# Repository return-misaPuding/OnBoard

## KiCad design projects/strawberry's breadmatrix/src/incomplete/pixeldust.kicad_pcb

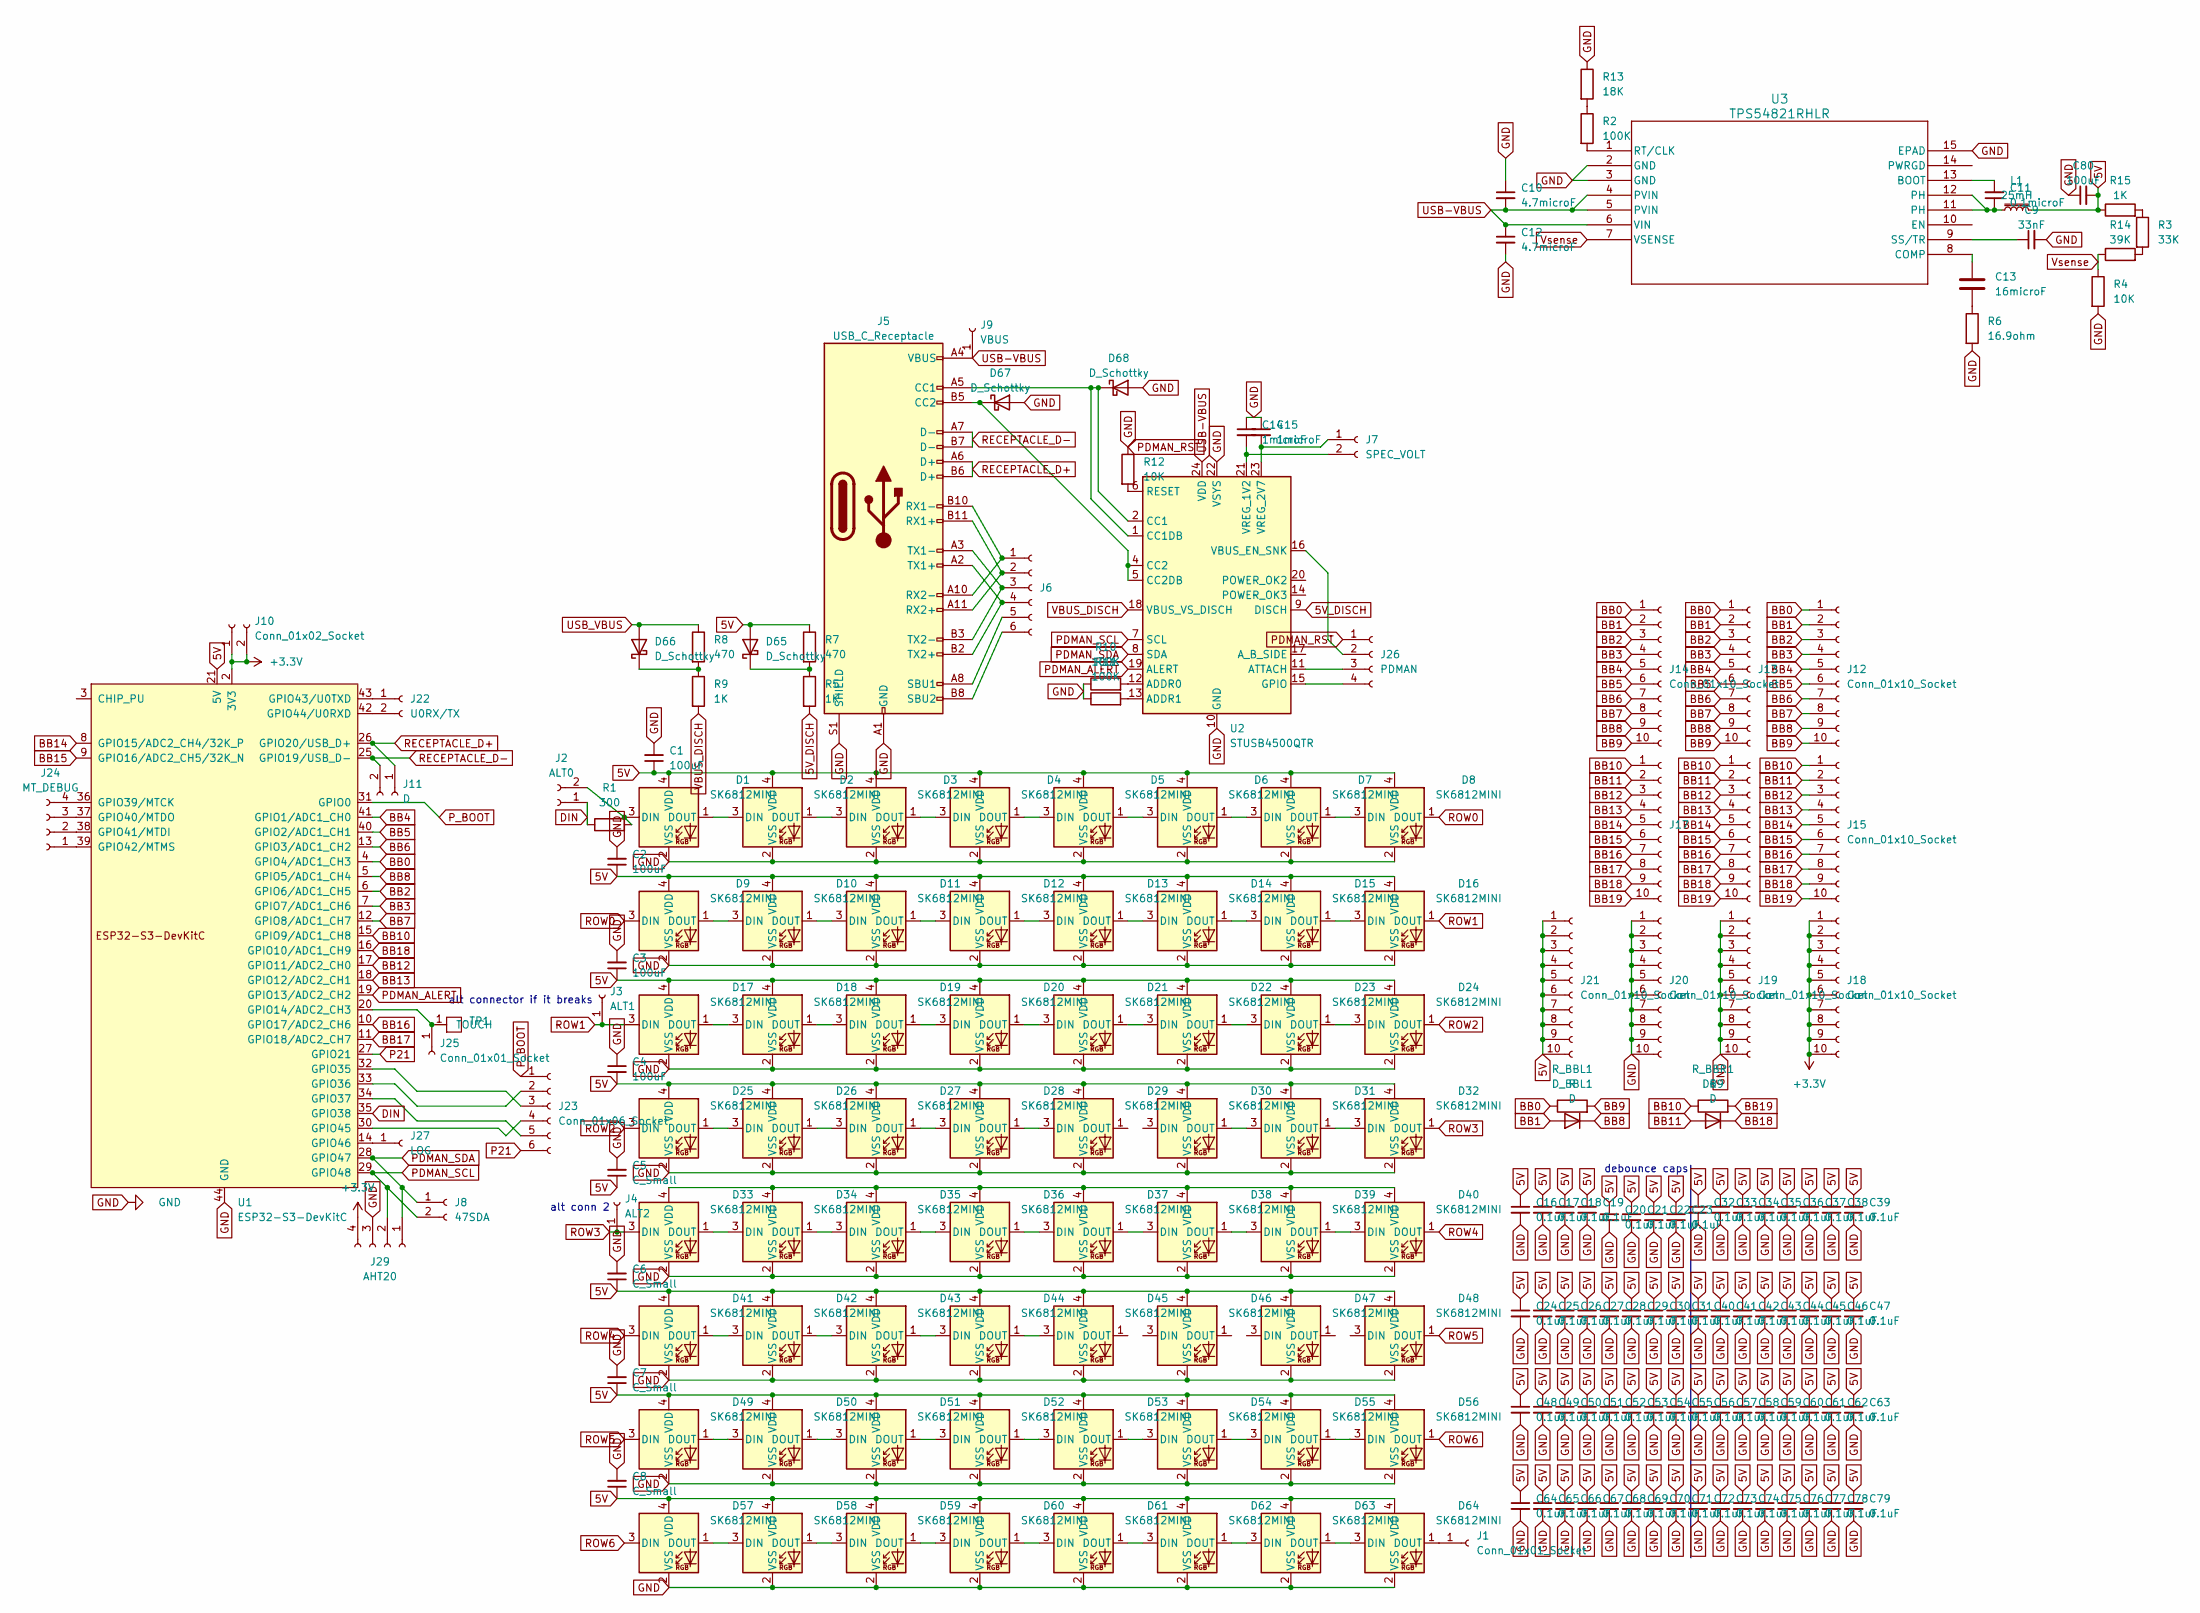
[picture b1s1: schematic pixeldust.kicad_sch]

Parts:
C1, C2, C3, C4, C80: 100uF; C_1206_3216Metric
C5, C6, C7, C8: C_Small; C_1206_3216Metric
C9: 33nF; C_0402_1005Metric
C10, C12: 4.7microF; C_1206_3216Metric_Pad1.33x1.80mm_HandSolder
C11: 0.1microF; C_0402_1005Metric
C13: 16microF; CP_Axial_L10.0mm_D4.5mm_P15.00mm_Horizontal
C14, C15: 1microF; C_0402_1005Metric
C16, C17, C18, C19, C20, C21, C22, C23, C24, C25, C26, C27, C28, C29, C30, C31, C32, C33, C34, C35, C36, C37, C38, C39, C40, C41, C42, C43, C44, C45, C46, C47, C48, C49, C50, C51, C52, C53, C54, C55, C56, C57, C58, C59, C60, C61, C62, C63, C64, C65, C66, C67, C68, C69, C70, C71, C72, C73, C74, C75, C76, C77, C78, C79: 0.1uF; C_0402_1005Metric
D1, D2, D3, D4, D5, D6, D7, D8, D9, D10, D11, D12, D13, D14, D15, D16, D17, D18, D19, D20, D21, D22, D23, D24, D25, D26, D27, D28, D29, D30, D31, D32, D33, D34, D35, D36, D37, D38, D39, D40, D41, D42, D43, D44, D45, D46, D47, D48, D49, D50, D51, D52, D53, D54, D55, D56, D57, D58, D59, D60, D61, D62, D63, D64: SK6812MINI; LED_SK6812MINI_PLCC4_3.5x3.5mm_P1.75mm
D65, D66: D_Schottky; D_DO-41_SOD81_P7.62mm_Horizontal
D67, D68: D_Schottky; D_DO-41_SOD81_P3.81mm_Vertical_AnodeUp
D69: D; D_SOD-123
D_BBL1: D; D_DO-41_SOD81_P3.81mm_Vertical_AnodeUp
J1, J25: Conn_01x01_Socket; PinSocket_1x01_P2.54mm_Vertical
J2: ALT0; PinSocket_1x02_P1.00mm_Vertical
J3: ALT1; PinSocket_1x01_P2.54mm_Vertical
J4: ALT2; PinSocket_1x01_P2.54mm_Vertical
J5: USB_C_Receptacle; USB_C_Receptacle_Amphenol_12401610E4-2A
J6: USBC_RX/TX; PinSocket_2x03_P1.27mm_Vertical
J7: SPEC_VOLT; PinSocket_1x02_P1.00mm_Vertical
J8: 47SDA; PinSocket_1x02_P1.00mm_Vertical
J9: VBUS; PinSocket_1x01_P2.54mm_Vertical
J10: Conn_01x02_Socket; PinSocket_1x02_P1.00mm_Vertical
J11: D; PinSocket_1x02_P1.00mm_Vertical
J12, J13, J14, J15, J16, J17, J18, J19, J20, J21: Conn_01x10_Socket; PinSocket_1x10_P2.54mm_Vertical
J22: U0RX/TX; PinSocket_1x02_P1.00mm_Vertical
J23: Conn_01x06_Socket; PinSocket_1x06_P1.00mm_Vertical
J24: MT_DEBUG; PinSocket_1x04_P1.00mm_Vertical
J26: PDMAN; PinSocket_2x02_P1.27mm_Vertical
J27: LOG; PinSocket_1x01_P2.54mm_Vertical
J29: AHT20; Adafruit_AHT20
L1: 25mH; L_10.4x10.4_H4.8
R1: 300; R_0402_1005Metric
R2, R10, R11: 100K; R_0402_1005Metric
R3: 33K; R_2512_6332Metric
R4: 10K; R_2512_6332Metric
R5, R9, R15: 1K; R_2512_6332Metric
R6: 16.9ohm; R_0603_1608Metric
R7, R8: 470; R_2512_6332Metric
R12: 10K; R_0402_1005Metric_Pad0.72x0.64mm_HandSolder
R13: 18K; R_0402_1005Metric
R14: 39K; R_2512_6332Metric
R_BBL1: R; R_Axial_DIN0207_L6.3mm_D2.5mm_P7.62mm_Horizontal
R_BBR1: R; R_2512_6332Metric_Pad1.40x3.35mm_HandSolder
TP1: TOUCH
U1: ESP32-S3-DevKitC
U2: STUSB4500QTR; QFN-24-1EP_4x4mm_P0.5mm_EP2.7x2.7mm
U3: TPS54821RHLR; RHL14_2P05X2P05

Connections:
5V: C1.1, C2.1, C3.1, C4.2, C5.1, C6.1, C7.1, C8.1, C16.1, C17.1, C18.1, C19.1, C20.1, C21.1, C22.1, C23.1, C24.1, C25.1, C26.1, C27.1, C28.1, C29.1, C30.1, C31.1, C32.1, C33.1, C34.1, C35.1, C36.1, C37.1, C38.1, C39.1, C40.1, C41.1, C42.1, C43.1, C44.1, C45.1, C46.1, C47.1, C48.1, C49.1, C50.1, C51.1, C52.1, C53.1, C54.1, C55.1, C56.1, C57.1, C58.1, C59.1, C60.1, C61.1, C62.1, C63.1, C64.1, C65.1, C66.1, C67.1, C68.1, C69.1, C70.1, C71.1, C72.1, C73.1, C74.1, C75.1, C76.1, C77.1, C78.1, C79.1, C80.2, D1.4 (VDD), D2.4 (VDD), D3.4 (VDD), D4.4 (VDD), D5.4 (VDD), D6.4 (VDD), D7.4 (VDD), D8.4 (VDD), D9.4 (VDD), D10.4 (VDD), D11.4 (VDD), D12.4 (VDD), D13.4 (VDD), D14.4 (VDD), D15.4 (VDD), D16.4 (VDD), D17.4 (VDD), D18.4 (VDD), D19.4 (VDD), D20.4 (VDD), D21.4 (VDD), D22.4 (VDD), D23.4 (VDD), D24.4 (VDD), D25.4 (VDD), D26.4 (VDD), D27.4 (VDD), D28.4 (VDD), D29.4 (VDD), D30.4 (VDD), D31.4 (VDD), D32.4 (VDD), D41.4 (VDD), D42.4 (VDD), D43.4 (VDD), D44.4 (VDD), D45.4 (VDD), D46.4 (VDD), D47.4 (VDD), D48.4 (VDD), D49.4 (VDD), D50.4 (VDD), D51.4 (VDD), D52.4 (VDD), D53.4 (VDD), D54.4 (VDD), D55.4 (VDD), D56.4 (VDD), D57.4 (VDD), D58.4 (VDD), D59.4 (VDD), D60.4 (VDD), D61.4 (VDD), D62.4 (VDD), D63.4 (VDD), D64.4 (VDD), D65.2 (A), J21.1, J21.2, J21.3, J21.4, J21.5, J21.6, J21.7, J21.8, J21.9, J21.10, L1.2, R7.1, R15.1, U1.21 (5V)
5V_DISCH: R5.2, U2.9 (DISCH)
+3.3V: J10.1, J10.2, J18.1, J18.2, J18.3, J18.4, J18.5, J18.6, J18.7, J18.8, J18.9, J18.10, J29.4, U1.1 (3V3), U1.2 (3V3)
BB0: J12.1, J13.1, J14.1, R_BBL1.1, U1.4 (GPIO4/ADC1_CH3)
BB1: D_BBL1.2 (A), J12.2, J13.2, J14.2
BB2: J12.3, J13.3, J14.3, U1.6 (GPIO6/ADC1_CH5)
BB3: J12.4, J13.4, J14.4, U1.7 (GPIO7/ADC1_CH6)
BB4: J12.5, J13.5, J14.5, U1.41 (GPIO1/ADC1_CH0)
BB5: J12.6, J13.6, J14.6, U1.40 (GPIO2/ADC1_CH1)
BB6: J12.7, J13.7, J14.7, U1.13 (GPIO3/ADC1_CH2)
BB7: J12.8, J13.8, J14.8, U1.12 (GPIO8/ADC1_CH7)
BB8: D_BBL1.1 (K), J12.9, J13.9, J14.9, U1.5 (GPIO5/ADC1_CH4)
BB9: J12.10, J13.10, J14.10, R_BBL1.2
BB10: J15.1, J16.1, J17.1, R_BBR1.1, U1.15 (GPIO9/ADC1_CH8)
BB11: D69.2 (A), J15.2, J16.2, J17.2
BB12: J15.3, J16.3, J17.3, U1.17 (GPIO11/ADC2_CH0)
BB13: J15.4, J16.4, J17.4, U1.18 (GPIO12/ADC2_CH1)
BB14: J15.5, J16.5, J17.5, U1.8 (GPIO15/ADC2_CH4/32K_P)
BB15: J15.6, J16.6, J17.6, U1.9 (GPIO16/ADC2_CH5/32K_N)
BB16: J15.7, J16.7, J17.7, U1.10 (GPIO17/ADC2_CH6)
BB17: J15.8, J16.8, J17.8, U1.11 (GPIO18/ADC2_CH7)
BB18: D69.1 (K), J15.9, J16.9, J17.9, U1.16 (GPIO10/ADC1_CH9)
BB19: J15.10, J16.10, J17.10, R_BBR1.2
DIN: J2.1, R1.1, U1.35 (GPIO38)
GND: C1.2, C2.2, C3.2, C4.1, C5.2, C6.2, C7.2, C8.2, C9.2, C10.1, C12.2, C14.1, C15.1, C16.2, C17.2, C18.2, C19.2, C20.2, C21.2, C22.2, C23.2, C24.2, C25.2, C26.2, C27.2, C28.2, C29.2, C30.2, C31.2, C32.2, C33.2, C34.2, C35.2, C36.2, C37.2, C38.2, C39.2, C40.2, C41.2, C42.2, C43.2, C44.2, C45.2, C46.2, C47.2, C48.2, C49.2, C50.2, C51.2, C52.2, C53.2, C54.2, C55.2, C56.2, C57.2, C58.2, C59.2, C60.2, C61.2, C62.2, C63.2, C64.2, C65.2, C66.2, C67.2, C68.2, C69.2, C70.2, C71.2, C72.2, C73.2, C74.2, C75.2, C76.2, C77.2, C78.2, C79.2, C80.1, D1.2 (VSS), D2.2 (VSS), D3.2 (VSS), D4.2 (VSS), D5.2 (VSS), D6.2 (VSS), D7.2 (VSS), D8.2 (VSS), D9.2 (VSS), D10.2 (VSS), D11.2 (VSS), D12.2 (VSS), D13.2 (VSS), D14.2 (VSS), D15.2 (VSS), D16.2 (VSS), D17.2 (VSS), D18.2 (VSS), D19.2 (VSS), D20.2 (VSS), D21.2 (VSS), D22.2 (VSS), D23.2 (VSS), D24.2 (VSS), D25.2 (VSS), D26.2 (VSS), D27.2 (VSS), D28.2 (VSS), D29.2 (VSS), D30.2 (VSS), D31.2 (VSS), D32.2 (VSS), D33.2 (VSS), D34.2 (VSS), D35.2 (VSS), D36.2 (VSS), D37.2 (VSS), D38.2 (VSS), D39.2 (VSS), D40.2 (VSS), D41.2 (VSS), D42.2 (VSS), D43.2 (VSS), D44.2 (VSS), D45.2 (VSS), D46.2 (VSS), D47.2 (VSS), D48.2 (VSS), D49.2 (VSS), D50.2 (VSS), D51.2 (VSS), D52.2 (VSS), D53.2 (VSS), D54.2 (VSS), D55.2 (VSS), D56.2 (VSS), D57.2 (VSS), D58.2 (VSS), D59.2 (VSS), D60.2 (VSS), D61.2 (VSS), D62.2 (VSS), D63.2 (VSS), D64.2 (VSS), D67.2 (A), D68.2 (A), J5.A1 (GND), J5.A12 (GND), J5.B1 (GND), J5.B12 (GND), J5.S1 (SHIELD), J19.1, J19.2, J19.3, J19.4, J19.5, J19.6, J19.7, J19.8, J19.9, J19.10, J20.1, J20.2, J20.3, J20.4, J20.5, J20.6, J20.7, J20.8, J20.9, J20.10, J26.1, J29.3, R4.2, R6.2, R10.1, R11.1, R12.1, R13.1, U1.22 (GND), U1.23 (GND), U1.24 (GND), U1.44 (GND), U2.10 (GND), U2.22 (VSYS), U2.25 (GND), U3.2 (GND), U3.3 (GND), U3.15 (EPAD)
unnamed: C11.1, L1.1, U3.11 (PH), U3.12 (PH)
unnamed: C13.2, R6.1
unnamed: D1.3 (DIN), J2.2, R1.2
unnamed: D1.1 (DOUT), D2.3 (DIN)
unnamed: D2.1 (DOUT), D3.3 (DIN)
unnamed: D3.1 (DOUT), D4.3 (DIN)
unnamed: D4.1 (DOUT), D5.3 (DIN)
unnamed: D5.1 (DOUT), D6.3 (DIN)
unnamed: D6.1 (DOUT), D7.3 (DIN)
unnamed: D7.1 (DOUT), D8.3 (DIN)
unnamed: D9.1 (DOUT), D10.3 (DIN)
unnamed: D10.1 (DOUT), D11.3 (DIN)
unnamed: D11.1 (DOUT), D12.3 (DIN)
unnamed: D12.1 (DOUT), D13.3 (DIN)
unnamed: D13.1 (DOUT), D14.3 (DIN)
unnamed: D14.1 (DOUT), D15.3 (DIN)
unnamed: D15.1 (DOUT), D16.3 (DIN)
unnamed: D17.1 (DOUT), D18.3 (DIN)
unnamed: D18.1 (DOUT), D19.3 (DIN)
unnamed: D19.1 (DOUT), D20.3 (DIN)
unnamed: D20.1 (DOUT), D21.3 (DIN)
unnamed: D21.1 (DOUT), D22.3 (DIN)
unnamed: D22.1 (DOUT), D23.3 (DIN)
unnamed: D23.1 (DOUT), D24.3 (DIN)
unnamed: D25.1 (DOUT), D26.3 (DIN)
unnamed: D26.1 (DOUT), D27.3 (DIN)
unnamed: D27.1 (DOUT), D28.3 (DIN)
unnamed: D28.1 (DOUT), D29.3 (DIN)
unnamed: D30.1 (DOUT), D31.3 (DIN)
unnamed: D31.1 (DOUT), D32.3 (DIN)
unnamed: D33.1 (DOUT), D34.3 (DIN)
unnamed: D33.4 (VDD), D34.4 (VDD), D35.4 (VDD), D36.4 (VDD), D37.4 (VDD), D38.4 (VDD), D39.4 (VDD), D40.4 (VDD)
unnamed: D34.1 (DOUT), D35.3 (DIN)
unnamed: D35.1 (DOUT), D36.3 (DIN)
unnamed: D36.1 (DOUT), D37.3 (DIN)
unnamed: D37.1 (DOUT), D38.3 (DIN)
unnamed: D38.1 (DOUT), D39.3 (DIN)
unnamed: D39.1 (DOUT), D40.3 (DIN)
unnamed: D41.1 (DOUT), D42.3 (DIN)
unnamed: D42.1 (DOUT), D43.3 (DIN)
unnamed: D43.1 (DOUT), D44.3 (DIN)
unnamed: D44.1 (DOUT), D45.3 (DIN)
unnamed: D49.1 (DOUT), D50.3 (DIN)
unnamed: D50.1 (DOUT), D51.3 (DIN)
unnamed: D51.1 (DOUT), D52.3 (DIN)
unnamed: D52.1 (DOUT), D53.3 (DIN)
unnamed: D53.1 (DOUT), D54.3 (DIN)
unnamed: D54.1 (DOUT), D55.3 (DIN)
unnamed: D55.1 (DOUT), D56.3 (DIN)
unnamed: D57.1 (DOUT), D58.3 (DIN)
unnamed: D58.1 (DOUT), D59.3 (DIN)
unnamed: D59.1 (DOUT), D60.3 (DIN)
unnamed: D60.1 (DOUT), D61.3 (DIN)
unnamed: D61.1 (DOUT), D62.3 (DIN)
unnamed: D62.1 (DOUT), D63.3 (DIN)
unnamed: D63.1 (DOUT), D64.3 (DIN)
unnamed: D64.1 (DOUT), J1.1
unnamed: D65.1 (K), R5.1, R7.2
unnamed: D66.1 (K), R8.2, R9.1
unnamed: D67.1 (K), J5.B5 (CC2), U2.4 (CC2), U2.5 (CC2DB)
unnamed: D68.1 (K), J5.A5 (CC1), U2.1 (CC1DB), U2.2 (CC1)
unnamed: J5.A11 (RX2+), J5.B11 (RX1+), J6.2
unnamed: J5.A10 (RX2-), J5.B10 (RX1-), J6.1
unnamed: J5.A8 (SBU1), J6.5
unnamed: J5.B8 (SBU2), J6.6
unnamed: J5.A2 (TX1+), J5.B2 (TX2+), J6.4
unnamed: J5.A3 (TX1-), J5.B3 (TX2-), J6.3
unnamed: C15.2, J7.1, U2.23 (VREG_2V7)
unnamed: C14.2, J7.2, U2.21 (VREG_1V2)
unnamed: J22.1, U1.43 (GPIO43/U0TXD)
unnamed: J22.2, U1.42 (GPIO44/U0RXD)
unnamed: J23.2, U1.33 (GPIO36)
unnamed: J23.3, U1.32 (GPIO35)
unnamed: J23.4, U1.30 (GPIO45)
unnamed: J23.5, U1.34 (GPIO37)
unnamed: J24.1, U1.39 (GPIO42/MTMS)
unnamed: J24.2, U1.38 (GPIO41/MTDI)
unnamed: J24.3, U1.37 (GPIO40/MTDO)
unnamed: J24.4, U1.36 (GPIO39/MTCK)
unnamed: J25.1, TP1.1 (TOUCH), U1.20 (GPIO14/ADC2_CH3)
unnamed: J26.2, U2.16 (VBUS_EN_SNK)
unnamed: J26.3, U2.11 (ATTACH)
unnamed: J26.4, U2.15 (GPIO)
unnamed: J27.1, U1.14 (GPIO46)
unnamed: R2.1, R13.2
unnamed: R3.2, R14.2
unnamed: R3.1, R15.2
unnamed: R10.2, U2.12 (ADDR0)
unnamed: R11.2, U2.13 (ADDR1)
unnamed: R12.2, U2.6 (RESET)
unnamed: C11.2, U3.13 (BOOT)
unnamed: C13.1, U3.8 (COMP)
unnamed: R2.2, U3.1 (RT/CLK)
unnamed: C9.1, U3.9 (SS/TR)
P21: J23.6, U1.27 (GPIO21)
PDMAN_ALERT: U1.19 (GPIO13/ADC2_CH2), U2.19 (ALERT)
PDMAN_SCL: J8.2, J29.2, U1.29 (GPIO48), U2.7 (SCL)
PDMAN_SDA: J8.1, J29.1, U1.28 (GPIO47), U2.8 (SDA)
P_BOOT: J23.1, U1.31 (GPIO0)
RECEPTACLE_D+: J5.A6 (D+), J5.B6 (D+), J11.1, U1.26 (GPIO20/USB_D+)
RECEPTACLE_D-: J5.A7 (D-), J5.B7 (D-), J11.2, U1.25 (GPIO19/USB_D-)
ROW0: D8.1 (DOUT), D9.3 (DIN)
ROW1: D16.1 (DOUT), D17.3 (DIN), J3.1
ROW2: D24.1 (DOUT), D25.3 (DIN)
ROW3: D32.1 (DOUT), D33.3 (DIN), J4.1
ROW4: D40.1 (DOUT), D41.3 (DIN)
ROW5: D48.1 (DOUT), D49.3 (DIN)
ROW6: D56.1 (DOUT), D57.3 (DIN)
USB-VBUS: C10.2, C12.1, J5.A4 (VBUS), J5.A9 (VBUS), J5.B4 (VBUS), J5.B9 (VBUS), J9.1, U2.24 (VDD), U3.4 (PVIN), U3.5 (PVIN), U3.6 (VIN)
USB_VBUS: D66.2 (A), R8.1
VBUS_DISCH: R9.2, U2.18 (VBUS_VS_DISCH)
Vsense: R4.1, R14.1, U3.7 (VSENSE)

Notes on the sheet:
alt connector if it breaks
debounce caps
alt conn 2

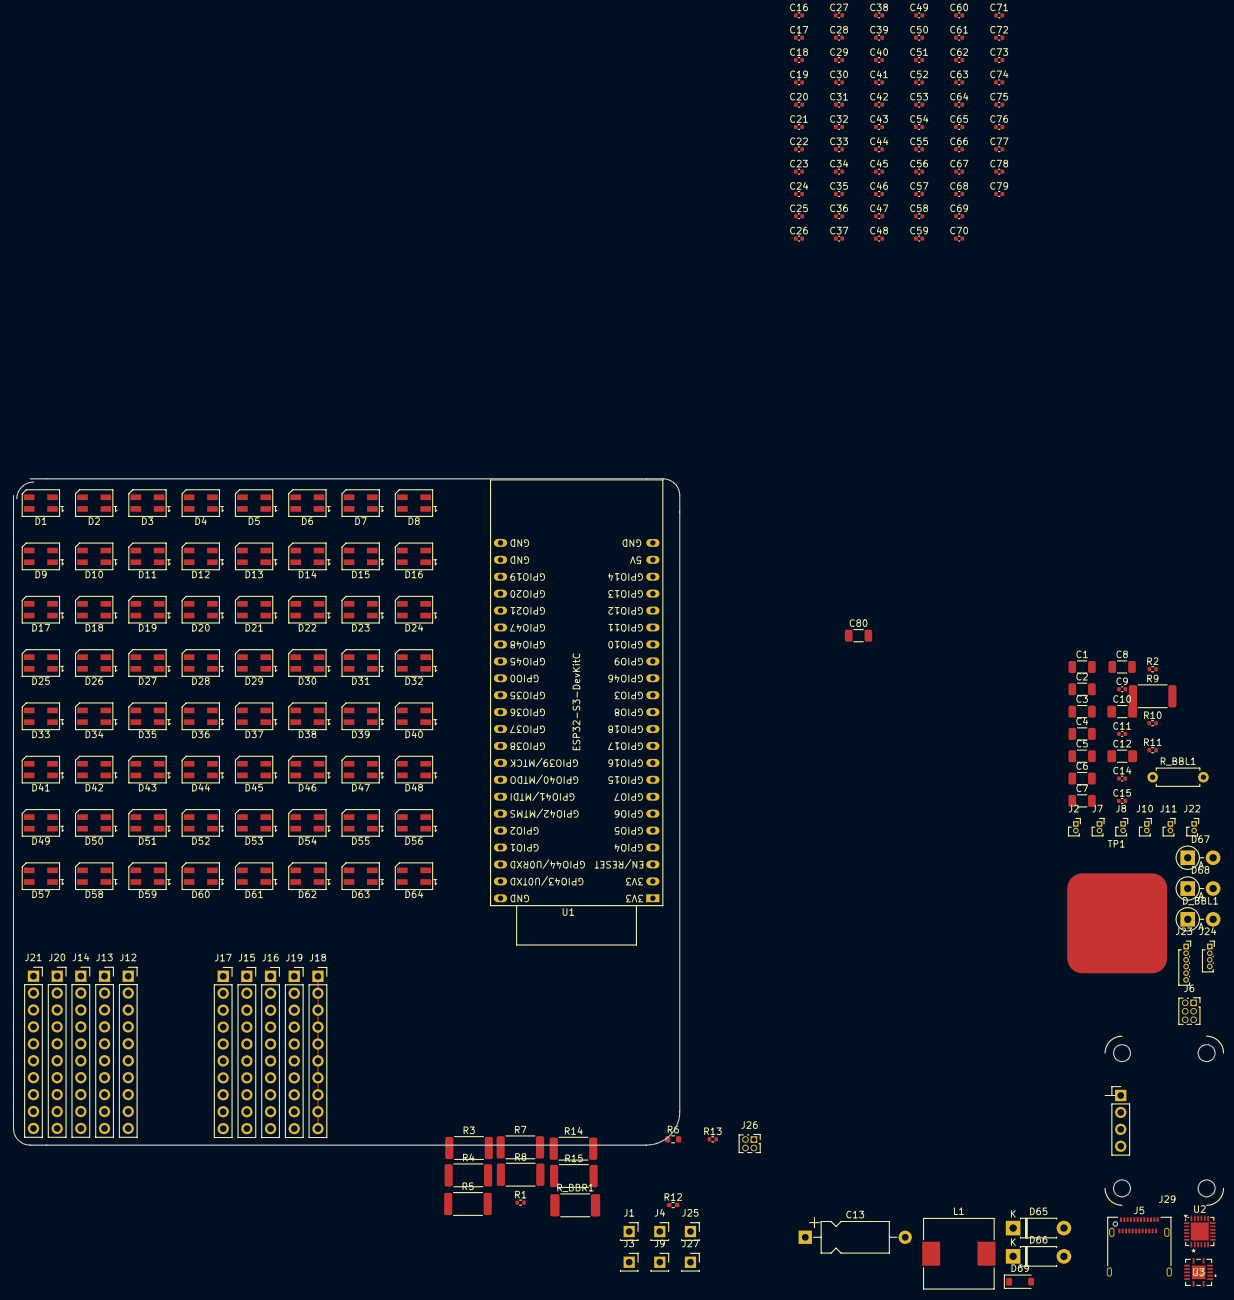
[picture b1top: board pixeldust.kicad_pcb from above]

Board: 2 copper layers, 200 parts (0 on the bottom side), 137 nets.

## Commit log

2025-04-30 add directory
2025-04-30 Add src files
